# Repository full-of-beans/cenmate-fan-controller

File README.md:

# CENMATE 6-Bay HDD Enclosure Fan Controller

Custom cooling and power-monitoring controller for a **CENMATE six-bay USB HDD enclosure (JBOD/DAS)**.

> **Prototype design in review.** The KiCad 10 schematic and PCB are implemented in the open [PCB PR #6](https://github.com/full-of-beans/cenmate-fan-controller/pull/6). Do not treat the design as production-qualified or order fabrication without checking the latest PR audit, ERC/DRC, manufacturing files, and mechanical fit. Older verification documents describe superseded revisions.

## Current design

- **Controller:** Seeed Studio XIAO RP2350, powered from the enclosure's USB-A 5 V supply through its USB-C connector. There is **no onboard TRACO 12 V-to-5 V converter** and no external 5 V connection to the module's VBUS pin. USB availability also provides the fan-switch enable signal.
- **Fans:** Two independently controlled 12 V, four-wire PWM fans, with separate PWM drive and tachometer inputs. The intended physical fan headers are [MODDIY 2.54 mm right-angle 4-pin male fan connectors](https://www.moddiy.com/products/5408/4-Pin-3-Pin-2.54mm-Pitch-2510-Fan-Male-Angled-Connector-Black.html). **The PCB still uses Molex right-angle header footprints/3D models as placeholders; the MODDIY parts have not been physically verified against those holes or pin orientation.** Do not purchase/install the Molex parts based on the current CAD representation.
- **Fan power:** TPS22810 high-side load switch controls the 12 V fan branch. Its EN is driven from USB VBUS, with a pull-down so fans are switched off when USB power is absent. PWM duty mapping and safe startup/reset behavior require firmware and bench verification.
- **Temperature sensing:** Two on-board 10 kΩ NTC thermistors, each read on its own XIAO ADC input through a 33 kΩ pull-up. There is **no remote thermistor strip or analog multiplexer**.
- **Current monitor:** TI INA228 on I²C, sensing the HDD backplane's positive 12 V feed through a **1 mΩ Bourns shunt**. The fan supply branches before the shunt, so the shunt measures the HDD branch rather than fan current. Accuracy and Kelvin/landing resistance must be checked by calibration.
- **HDD power path:** Center-positive 12 V barrel input **J1** → shunt **RSH1** → Phoenix Contact two-position screw terminal **J2** → HDD enclosure. **J2 pin 1 = +12 V, pin 2 = GND.** The PCB has explicit `12V` and `GND` silkscreen markings beside J2; verify wiring polarity before connection.
- **Grounding:** Common system ground, with a two-layer PCB and ground copper fill.

The enclosure's power brick is labeled **12 V / 9 A**. The selected **Tensility 54-00286 barrel jack is rated 7 A**; the owner has explicitly accepted the prototype risk rather than replacing it. This does **not** establish that six-drive startup and operating loads meet the connector rating. Measure the actual current, contact voltage drop, and connector heating during controlled bring-up.

## Hardware and mechanical status

The board and custom backplate have been checked for fit by the owner in Onshape. This does not independently verify fabricated edge reliefs, actual mated MODDIY connector geometry, cable bends, or as-built tolerances. Check physical fit before connecting the HDD enclosure.

The prototype PCB is intended for **JLCPCB standard two-layer, 1 oz copper, green solder mask**. The green-mask choice accommodates the nominal 0.12 mm solder-mask web between Q1/Q2 pads under the cited 0.10 mm green-mask limit; review the final manufacturer CAM preview. Existing silkscreen and exposed component/connector pads are accepted for prototype testing without adding dedicated test-point footprints.

## Repository layout

```text
hardware/
  fan-controller.kicad_pro   KiCad 10 project
  fan-controller.kicad_sch   Current controller schematic
  fan-controller.kicad_pcb   Current PCB layout
  fan-controller.kicad_dru   Custom DRC rules
  libraries/                 Project-local symbols, footprints, and models
firmware/                   Controller firmware (as developed)
docs/                       Design notes, reviews, and historical verification
mechanical/                 Mechanical files (as available)
```

Open `hardware/fan-controller.kicad_pro` with **KiCad 10**. The project-local `FanController` libraries must resolve before editing or plotting. The retired remote-sensor-strip design and earlier TRACO-based architecture are **historical only**; do not follow them when building the current board.

## Prototype release and validation checklist

Before ordering:

1. Review the latest findings and owner dispositions in [PR #6](https://github.com/full-of-beans/cenmate-fan-controller/pull/6). Original audit: [pre-fabrication engineering review](https://github.com/full-of-beans/cenmate-fan-controller/pull/6#pullrequestreview-5802921394).
2. Run KiCad 10 schematic ERC and PCB DRC with schematic parity checks on the **current commit**, not just historical reports. Review all remaining warnings and exceptions.
3. Verify symbol/PCB footprint correspondence, BOM/manufacturer part numbers, and J1/J2 and fan-header pin mapping. The MODDIY header's actual lead pattern, orientation, mating and retention remain unverified.
4. Plot and inspect copper, solder-mask, silkscreen, Edge.Cuts, and drill files. Confirm cutout and mounting-hole geometry in the manufacturer's preview; select **green solder mask and 1 oz copper**.
5. Check assembly access and the physical backplate, fan, USB, barrel plug, and screw-terminal clearances.

Before connecting drives, perform continuity and polarity checks, current-limited initial power-up, USB-present/absent versus 12 V-present/absent sequencing, fan enable/PWM/tach tests, INA228 communication and calibration, and thermistor checks. Only then test with the enclosure under controlled startup/full-load conditions while monitoring the accepted 7 A connector risk.

## Documentation provenance

[Controller schematic verification](docs/controller-schematic-verification.md) and earlier PR reviews are retained for engineering history; some sections describe **superseded architectures, parts and pin mappings**. The active schematic/PCB on the latest PR commit and its current review/disposition comments take precedence. Fan-control firmware strategy (fan curve versus PI) remains undecided pending modeling and comparison.

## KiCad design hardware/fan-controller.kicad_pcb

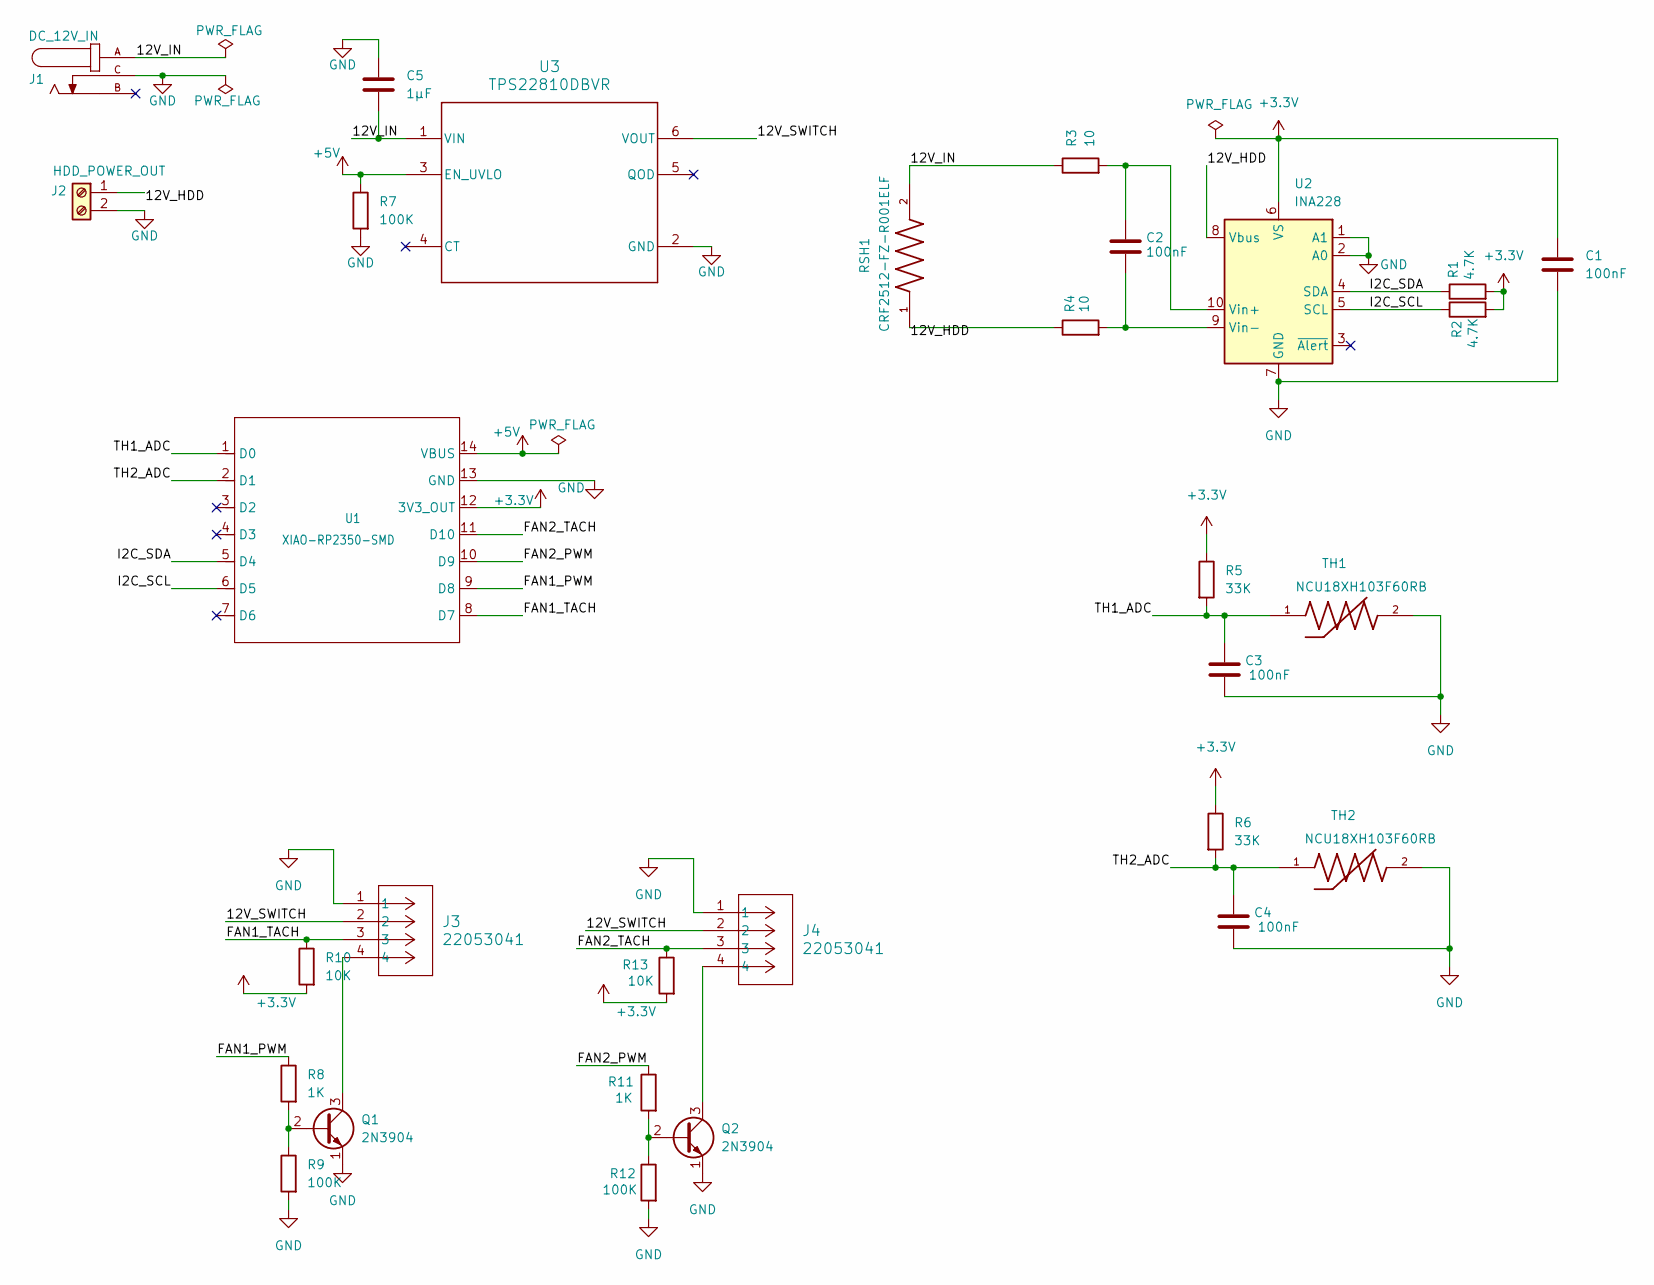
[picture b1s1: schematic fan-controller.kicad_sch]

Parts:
C1, C2, C3, C4: 100nF; C_0805_2012Metric; MPN CL21B104KACNFNC; DigiKey_PN 1276-2442-1-ND
C5: 1µF; C_0805_2012Metric; MPN GRM219R71E105KA88D; DigiKey_PN 490-5899-1-ND
J1: DC_12V_IN; TENSILITY_54-00286; MPN 54-00286; DigiKey_PN 839-54-00286-ND
J2: HDD_POWER_OUT; PHOENIX_5442206; MPN 5442206; DigiKey_PN 277-12547-ND
J3, J4: 22053041; CONN_A-7478-04A_MOL; MPN 0022053041; DigiKey_PN WM4302-ND
Q1, Q2: 2N3904; TO-92_Inline; MPN 2N3904BU; DigiKey_PN 2N3904FS-ND
R1, R2: 4.7K; R_0805_2012Metric; MPN RC0805FR-074K7L; DigiKey_PN 311-4.70KCRCT-ND
R3, R4: 10; R_0805_2012Metric; MPN RC0805FR-0710RL; DigiKey_PN 311-10.0CRCT-ND
R5, R6: 33K; R_0805_2012Metric; MPN RC0805FR-0733KL; DigiKey_PN 311-33.0KCRCT-ND
R7, R9, R12: 100K; R_0805_2012Metric; MPN RC0805FR-07100KL; DigiKey_PN 311-100KCRCT-ND
R8, R11: 1K; R_0805_2012Metric; MPN RC0805FR-071KL; DigiKey_PN 311-1.00KCRCT-ND
R10, R13: 10K; R_0805_2012Metric; MPN RC0805FR-0710KL; DigiKey_PN 311-10.0KCRCT-ND
RSH1: CRF2512-FZ-R001ELF; RESC6432X80N; MPN CRF2512-FZ-R001ELF; DigiKey_PN CRF2512-FZ-R001ELFCT-ND
TH1, TH2: NCU18XH103F60RB; THRMC1608X95N; MPN NCU18XH103F60RB; DigiKey_PN 490-16279-1-ND
U1: XIAO-RP2350-SMD; XIAO-RP2350-no-underside; MPN 102010550; DigiKey_PN 1597-102010550-ND
U2: INA228; TSSOP-10_3x3mm_P0.5mm; MPN INA228AIDGSR; DigiKey_PN 296-INA228AIDGSRCT-ND
U3: TPS22810DBVR; MPN TPS22810DBVR; DigiKey_PN 296-45297-1-ND

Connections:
+3.3V: C1.1, R1.2, R2.2, R5.1, R6.1, R10.2, R13.2, U1.12 (3V3_OUT), U2.6 (VS)
+5V: R7.1, U1.14 (VBUS), U3.3 (EN_UVLO)
/12V_HDD: J2.1, R4.1, RSH1.1, U2.8 (Vbus)
/12V_IN: C5.2, J1.A, R3.1, RSH1.2, U3.1 (VIN)
/12V_SWITCH: J3.2, J4.2, U3.6 (VOUT)
/FAN1_PWM: R8.1, U1.9 (D8)
/FAN1_TACH: J3.3, R10.1, U1.8 (D7)
/FAN2_PWM: R11.1, U1.10 (D9)
/FAN2_TACH: J4.3, R13.1, U1.11 (D10)
/I2C_SCL: R2.1, U1.6 (D5), U2.5 (SCL)
/I2C_SDA: R1.1, U1.5 (D4), U2.4 (SDA)
/TH1_ADC: C3.1, R5.2, TH1.1, U1.1 (D0)
/TH2_ADC: C4.1, R6.2, TH2.1, U1.2 (D1)
GND: C1.2, C3.2, C4.2, C5.1, J1.C, J2.2, J3.1, J4.1, Q1.1 (E), Q2.1 (E), R7.2, R9.2, R12.2, TH1.2, TH2.2, U1.13 (GND), U2.1 (A1), U2.2 (A0), U2.7 (GND), U3.2 (GND); also elsewhere on the board
unnamed: Q1.2 (B), R8.2, R9.1
unnamed: J3.4, Q1.3 (C)
unnamed: Q2.2 (B), R11.2, R12.1
unnamed: J4.4, Q2.3 (C)
unnamed: C2.1, R3.2, U2.10 (Vin+)
unnamed: C2.2, R4.2, U2.9 (Vin-)

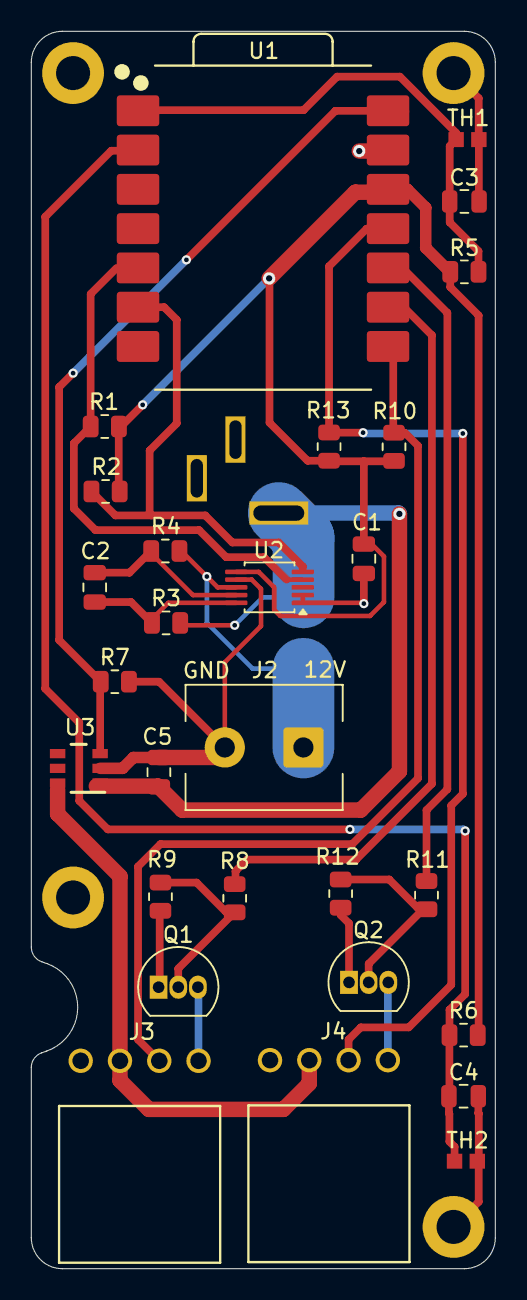
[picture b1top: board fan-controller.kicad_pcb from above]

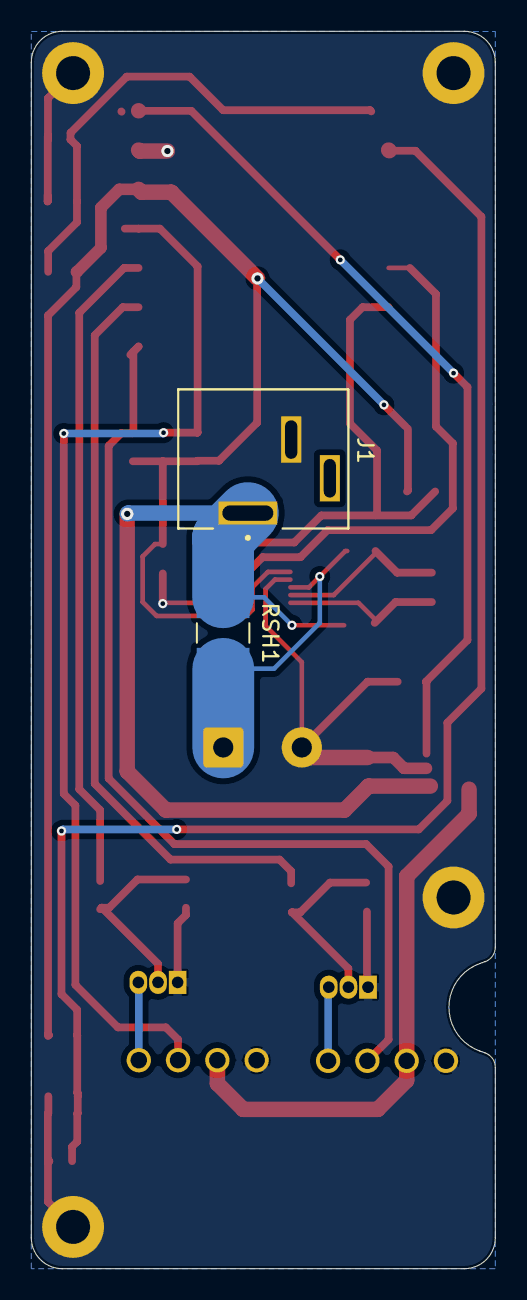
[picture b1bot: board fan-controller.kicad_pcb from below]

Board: 2 copper layers, 30.0 x 80.0 mm, 34 parts (2 on the bottom side), 20 nets.

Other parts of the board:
H1, H2, H3, H4: MountingHole_2.2mm_M2_Pad_4mm

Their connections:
GND: H1.1, H2.1, H3.1, H4.1; also elsewhere on the board

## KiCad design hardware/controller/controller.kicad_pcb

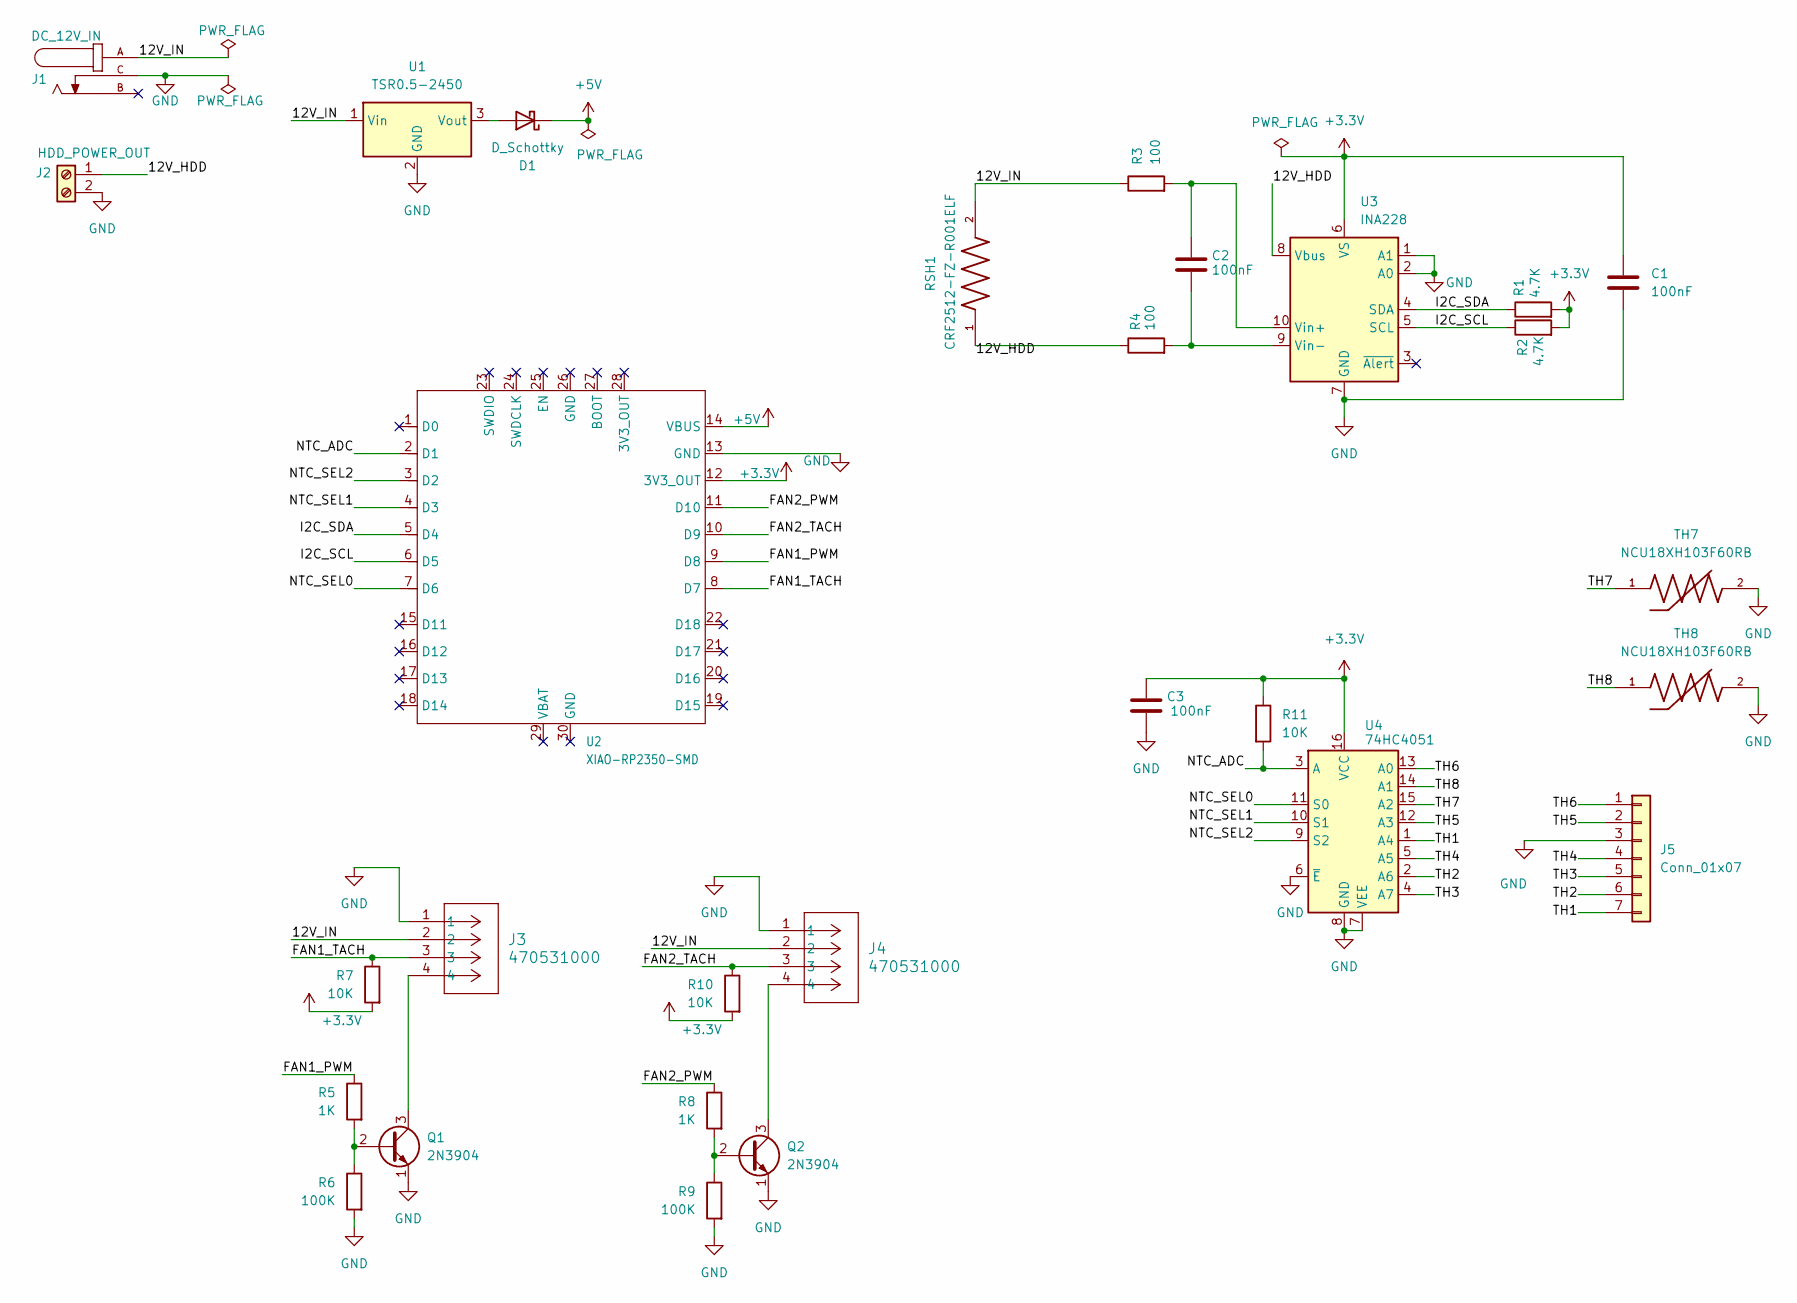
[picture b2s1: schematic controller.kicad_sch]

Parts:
C1, C2, C3: 100nF; C_0805_2012Metric
D1: D_Schottky; D_SOD-123F
J1: DC_12V_IN; TENSILITY_54-00286; PARTREV A
J2: HDD_POWER_OUT; TerminalBlock_Phoenix_MKDS-3-2-5.08_1x02_P5.08mm_Horizontal
J3, J4: 470531000; CONN_SD-47053-001_H10p00_MOL
J5: Conn_01x07; JST_ZH_B7B-ZR_1x07_P1.50mm_Horizontal
Q1, Q2: 2N3904; TO-92_Inline
R1, R2: 4.7K; R_0805_2012Metric
R3, R4: 100; R_0805_2012Metric
R5, R8: 1K; R_0805_2012Metric
R6, R9: 100K; R_0805_2012Metric
R7, R10, R11: 10K; R_0805_2012Metric
RSH1: CRF2512-FZ-R001ELF; RESC6432X80N
TH7, TH8: NCU18XH103F60RB; THRMC1608X95N
U1: TSR0.5-2450; Converter_DCDC_TRACO_TSR0.5-24xx_TSR0.5-24xxx_THT
U2: XIAO-RP2350-SMD; XIAO-RP2350-no-underside
U3: INA228; TSSOP-10_3x3mm_P0.5mm
U4: 74HC4051; SOIC-16_3.9x9.9mm_P1.27mm

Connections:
+3.3V: C1.1, C3.1, R1.2, R2.2, R7.2, R10.2, R11.1, U2.12 (3V3_OUT), U3.6 (VS), U4.16 (VCC)
+5V: D1.1 (K), U2.14 (VBUS)
/12V_HDD: J2.1, R4.1, RSH1.1, U3.8 (Vbus)
/12V_IN: J1.A, J3.2, J4.2, R3.1, RSH1.2, U1.1 (Vin)
/FAN1_PWM: R5.1, U2.9 (D8)
/FAN1_TACH: J3.3, R7.1, U2.8 (D7)
/FAN2_PWM: R8.1, U2.11 (D10)
/FAN2_TACH: J4.3, R10.1, U2.10 (D9)
/I2C_SCL: R2.1, U2.6 (D5), U3.5 (SCL)
/I2C_SDA: R1.1, U2.5 (D4), U3.4 (SDA)
/NTC_ADC: R11.2, U2.2 (D1), U4.3 (A)
/NTC_SEL0: U2.7 (D6), U4.11 (S0)
/NTC_SEL1: U2.4 (D3), U4.10 (S1)
/NTC_SEL2: U2.3 (D2), U4.9 (S2)
/TH1: J5.7, U4.1 (A4)
/TH2: J5.6, U4.2 (A6)
/TH3: J5.5, U4.4 (A7)
/TH4: J5.4, U4.5 (A5)
/TH5: J5.2, U4.12 (A3)
/TH6: J5.1, U4.13 (A0)
/TH7: TH7.1, U4.15 (A2)
/TH8: TH8.1, U4.14 (A1)
GND: C1.2, C3.2, J1.C, J2.2, J3.1, J4.1, J5.3, Q1.1 (E), Q2.1 (E), R6.2, R9.2, TH7.2, TH8.2, U1.2 (GND), U2.13 (GND), U3.1 (A1), U3.2 (A0), U3.7 (GND), U4.6 (~E), U4.7 (VEE), U4.8 (GND)
unnamed: D1.2 (A), U1.3 (Vout)
unnamed: Q1.2 (B), R5.2, R6.1
unnamed: J3.4, Q1.3 (C)
unnamed: Q2.2 (B), R8.2, R9.1
unnamed: J4.4, Q2.3 (C)
unnamed: C2.1, R3.2, U3.10 (Vin+)
unnamed: C2.2, R4.2, U3.9 (Vin-)

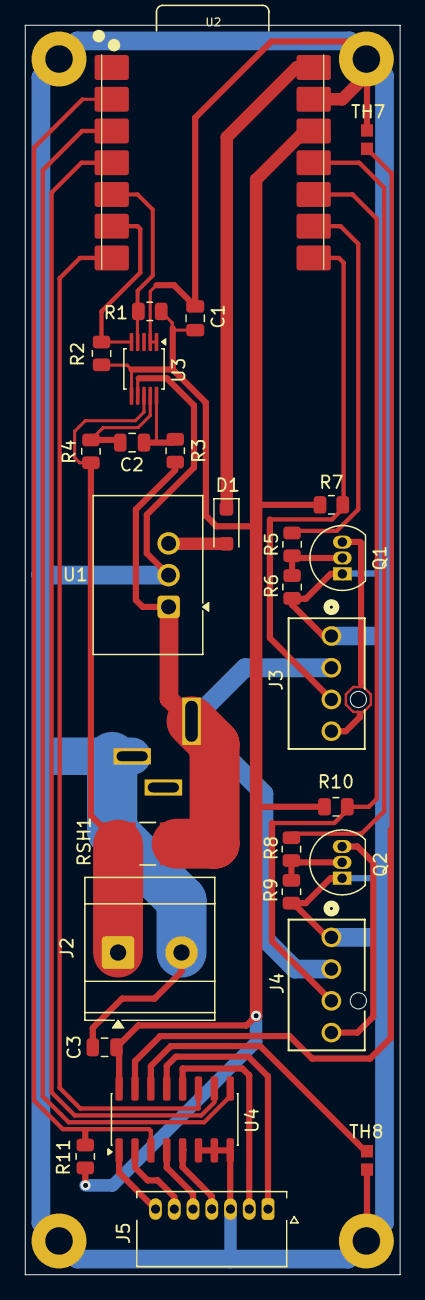
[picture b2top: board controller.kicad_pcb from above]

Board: 2 copper layers, 30.0 x 100.0 mm, 29 parts (1 on the bottom side), 30 nets.

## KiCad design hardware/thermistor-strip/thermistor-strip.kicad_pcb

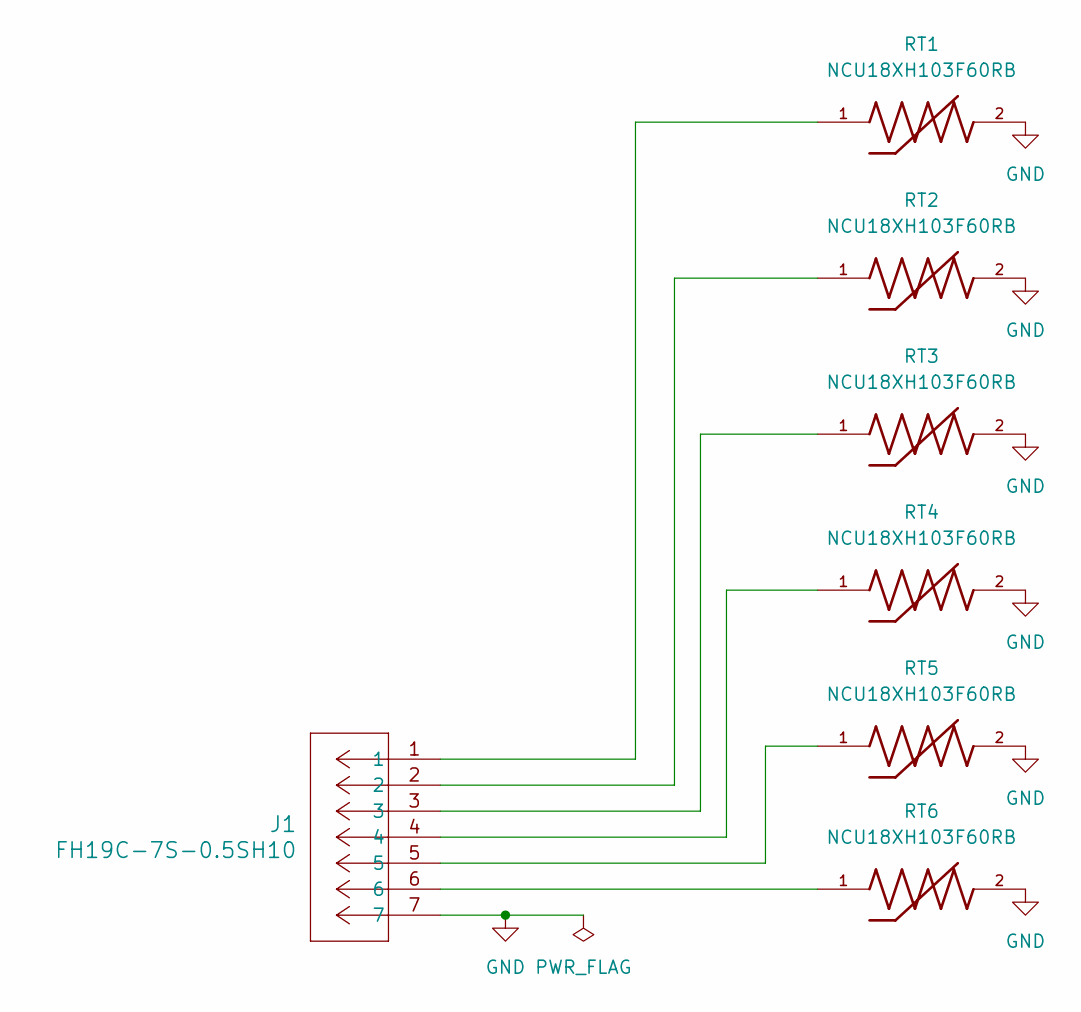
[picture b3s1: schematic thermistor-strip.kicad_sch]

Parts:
J1: FH19C-7S-0.5SH10; CONN7_FH19C_7S_HIR
RT1, RT2, RT3, RT4, RT5, RT6: NCU18XH103F60RB; THRMC1608X95N

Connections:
GND: J1.7, RT1.2, RT2.2, RT3.2, RT4.2, RT5.2, RT6.2
unnamed: J1.1, RT1.1
unnamed: J1.2, RT2.1
unnamed: J1.3, RT3.1
unnamed: J1.4, RT4.1
unnamed: J1.5, RT5.1
unnamed: J1.6, RT6.1

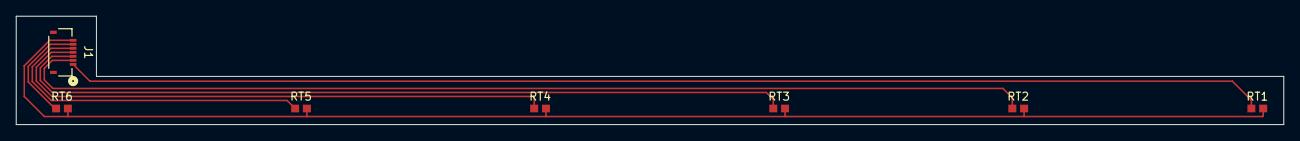
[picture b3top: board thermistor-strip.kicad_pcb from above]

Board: 2 copper layers, 158.0 x 13.5 mm, 7 parts (0 on the bottom side), 7 nets.
